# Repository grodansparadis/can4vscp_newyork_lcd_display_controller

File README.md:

<h1>New York - CAN4VSCP LCD display controller<h1>

CAN4VSCP controller that handle a LCD displays.

<hr>

This project is part of the <a href="http://www.vscp.org">VSCP (Very Simple Control Protocol) project</a>. 

<hr>

This project is licensed under the 
<a href="http://creativecommons.org/licenses/by-nc-sa/3.0/">Creative Commons open source license Attribution-NonCommercial-ShareAlike 3.0 Unported</a>. 
Other license options are available by conacting <a href="malto:info@grodansparadis.com">Paradis of the Frog AB</a>

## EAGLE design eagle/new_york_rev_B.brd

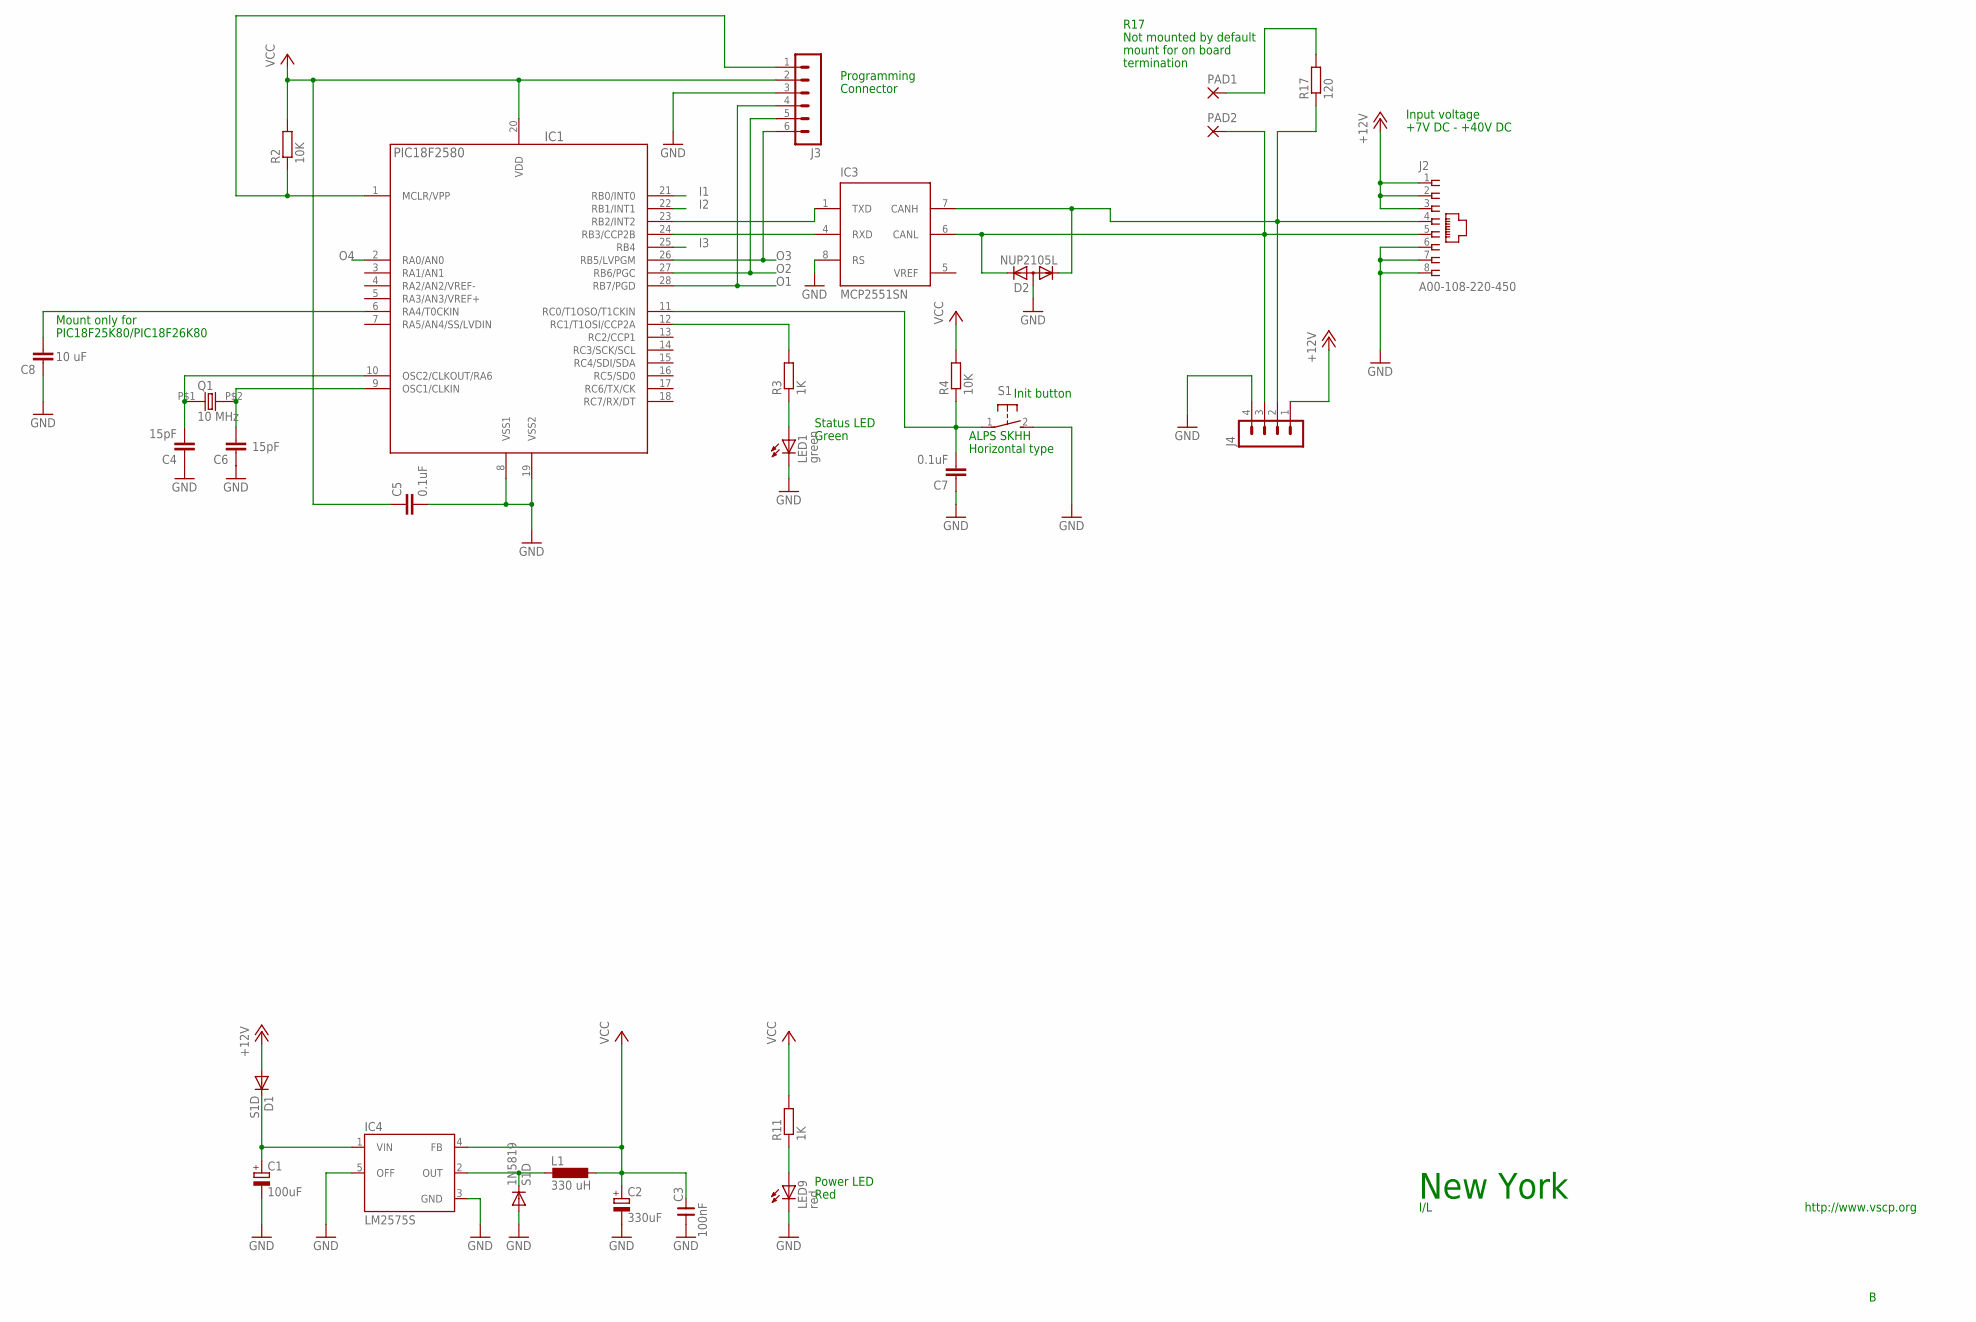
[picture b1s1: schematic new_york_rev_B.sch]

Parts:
1N5819: S1D; SOD123
C1: 100uF; PANASONIC_D
C2: 330uF; PANASONIC_D
C3: 100nF; 0805
C4, C6: 15pF; C0805
C5, C7: 0.1uF; C0805
C8: 10 uF; C0805
D1: S1D; SOD123
D2: NUP2105L; SOT23
IC1: PIC18F2580; SO28
IC3: MCP2551SN; SO-08
IC4: LM2575S; TO263-5
J2: A00-108-220-450; RJ-45
J3: MA06-1
J4: MA04-1
L1: 330 uH; DO3316P
LED1: green; CHIP-LED0805
LED9: red; CHIP-LED0805
PAD1, PAD2: 1,6/0,8
Q1: 10 MHz; 9C
R2, R4: 10K; R0805
R3, R11: 1K; R0805
R17: 120; R0805
S1: 31-XX; B3F-31XX

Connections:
+12V: D1.A, J2.1, J2.2, J2.3, J4.1
CANL: D2.2 (K2), IC3.6 (CANL), J2.5, J4.3, PAD2.1
GND: 1N5819.A, C1.-, C2.-, C3.1, C4.1, C5.2, C6.1, C7.1, C8.1, D2.3 (A), IC1.8 (VSS1), IC1.19 (VSS2), IC3.2 (VSS), IC3.8 (RS), IC4.3 (GND), IC4.5 (OFF), J2.6, J2.7, J2.8, J3.3, J4.4, LED1.C, LED9.C, S1.2 (S)
I1: IC1.21 (RB0/INT0)
I2: IC1.22 (RB1/INT1)
I3: IC1.25 (RB4)
unnamed: 1N5819.C, IC4.2 (OUT), L1.1
unnamed: C4.2, IC1.10 (OSC2/CLKOUT/RA6), Q1.P$1 (1)
unnamed: C1.+, D1.C, IC4.1 (VIN)
unnamed: IC1.12 (RC1/T1OSI/CCP2A), R3.2
unnamed: LED1.A, R3.1
unnamed: C7.2, IC1.11 (RC0/T1OSO/T1CKIN), R4.1, S1.1
unnamed: C6.2, IC1.9 (OSC1/CLKIN), Q1.P$2 (2)
unnamed: IC1.1 (MCLR/VPP), J3.1, R2.1
unnamed: LED9.A, R11.1
unnamed: C8.2, IC1.6 (RA4/T0CKIN)
unnamed: D2.1 (K1), IC3.7 (CANH), J2.4, J4.2, R17.1
unnamed: PAD1.1, R17.2
O1: IC1.28 (RB7/PGD), J3.4
O2: IC1.27 (RB6/PGC), J3.5
O3: IC1.26 (RB5/LVPGM), J3.6
O4: IC1.2 (RA0/AN0)
RXCAN: IC1.24 (RB3/CCP2B), IC3.4 (RXD)
TXCAN: IC1.23 (RB2/INT2), IC3.1 (TXD)
VCC: C2.+, C3.2, C5.1, IC1.20 (VDD), IC3.3 (VDD), IC4.4 (FB), J3.2, L1.2, R2.2, R4.2, R11.2
VREF: IC3.5 (VREF)

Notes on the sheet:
Init button
Status LED
Programming
Connector
ALPS SKHH
Horizontal type
New York
http://www.vscp.org
I/L
Input voltage
+7V DC - +40V DC
Power LED
Red
Green
Mount only for
PIC18F25K80/PIC18F26K80
Not mounted by default
mount for on board
termination
R17

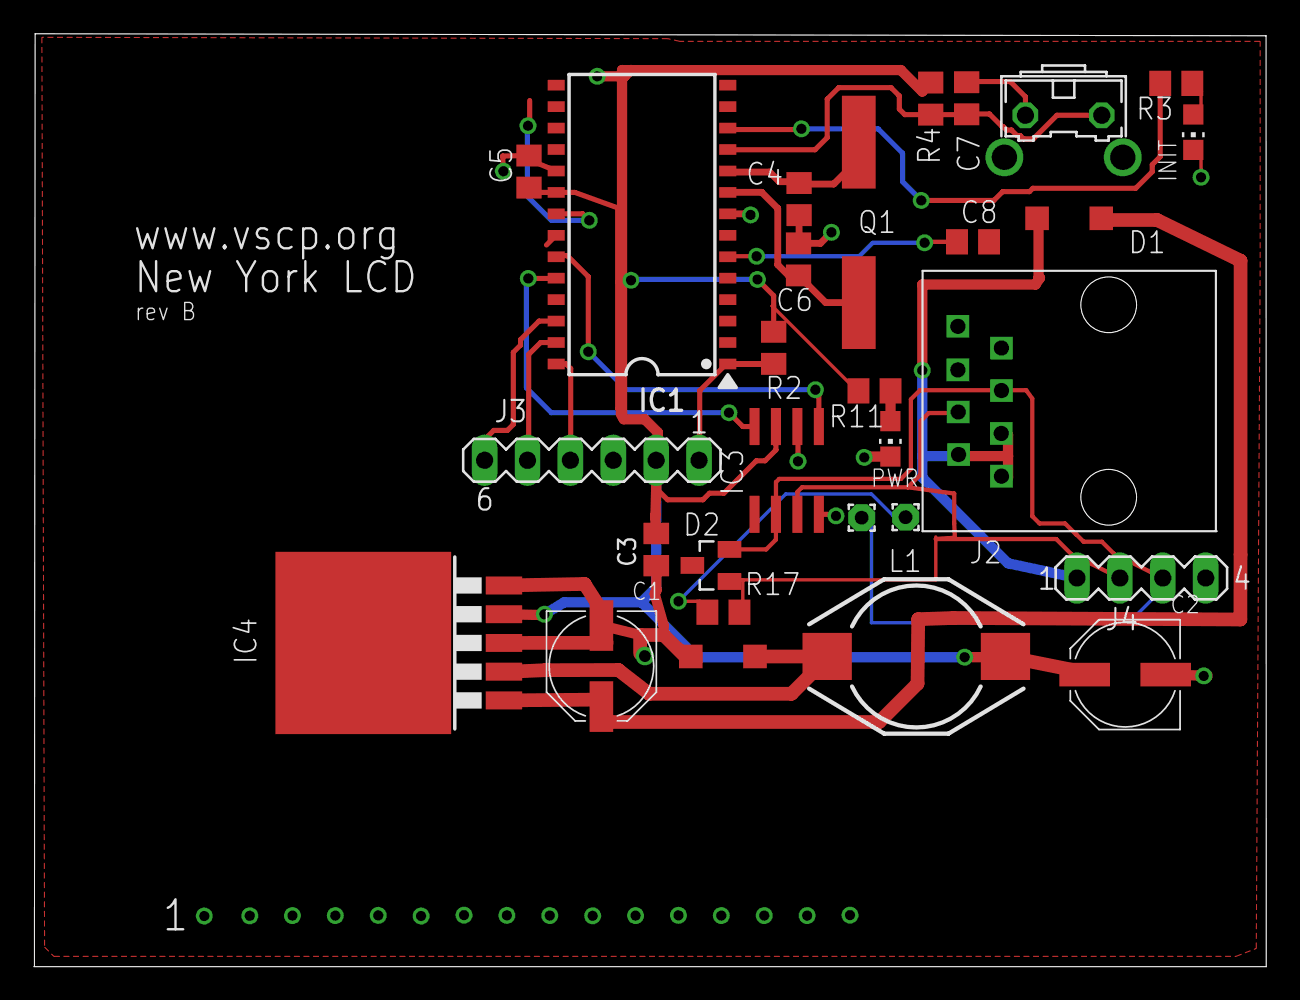
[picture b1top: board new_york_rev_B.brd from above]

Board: 2 copper layers, 73.0 x 55.2 mm, 29 parts (0 on the bottom side), 21 nets.

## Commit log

2015-08-29 Moved from private repository
2015-12-17 Updated license and readme
2016-04-04 Changed value of C14 to 10uF
